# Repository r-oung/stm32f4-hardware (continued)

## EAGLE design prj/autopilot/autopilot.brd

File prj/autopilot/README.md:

# Autopilot
A drone autopilot using the STM32F4 microcontroller.

The firmware for this project can be found in the [stm32f4-firmware repository](https://github.com/r-oung/stm32f4-firmware).

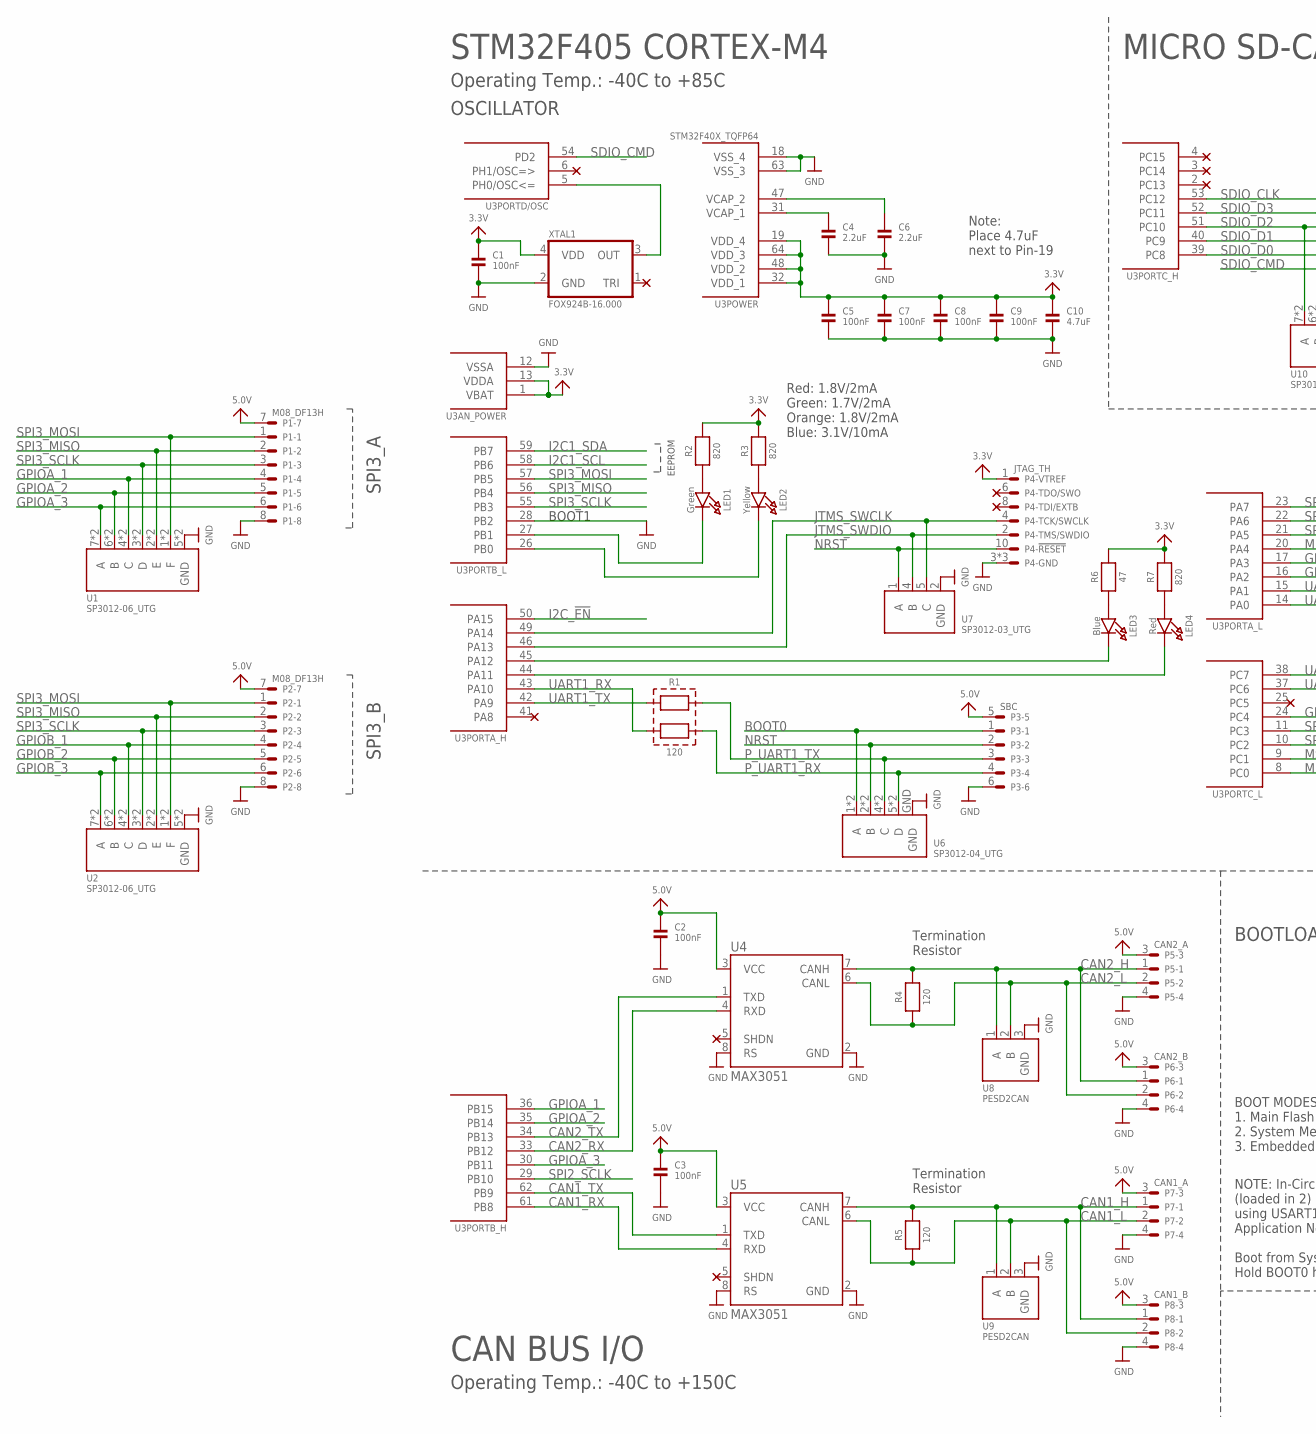
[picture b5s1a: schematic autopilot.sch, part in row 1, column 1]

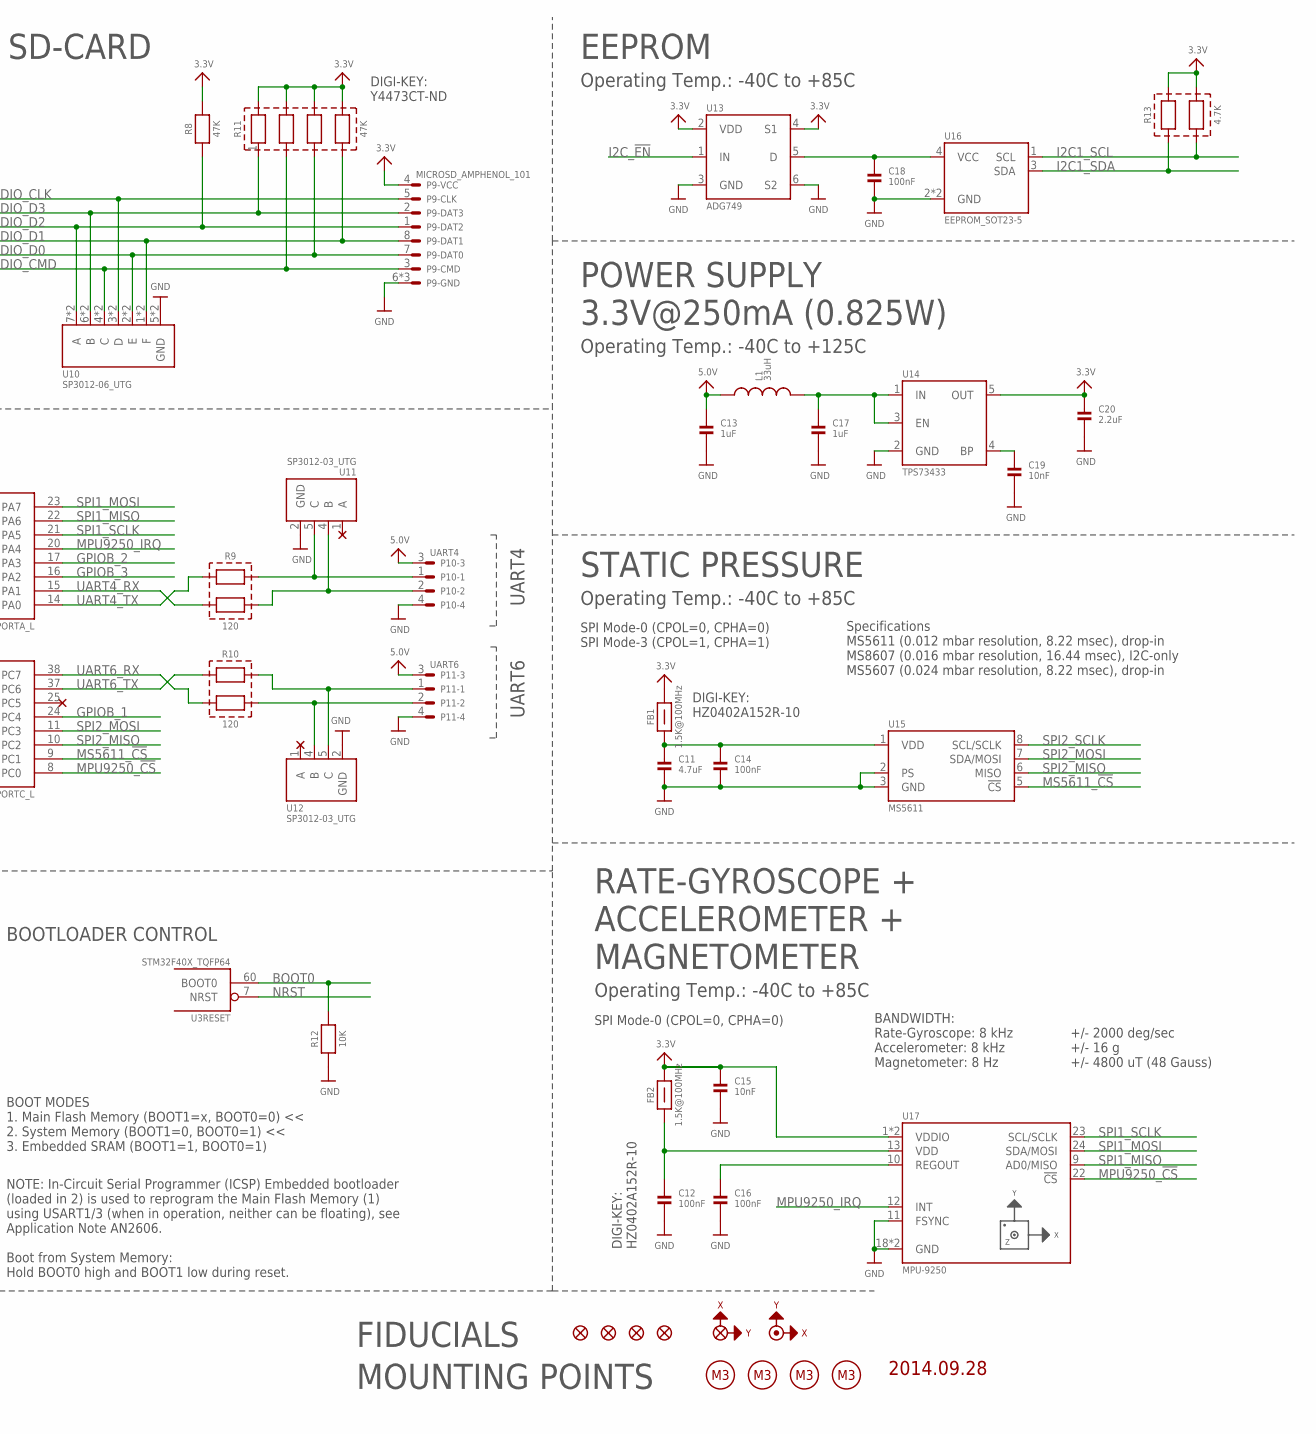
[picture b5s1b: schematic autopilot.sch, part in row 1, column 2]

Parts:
AXIS3D1: AXIS3D_DOWN
AXIS3D2: AXIS3D_UP
C1, C2, C3, C5, C7, C8, C9, C12, C14, C16, C18: 100nF; 0402
C4, C6, C20: 2.2uF; 0402
C10, C11: 4.7uF; 0402
C13, C17: 1uF; 0402
C15, C19: 10nF; 0402
FB1, FB2: 1.5K@100MHz; 0402
L1: 33uH; 1210
LED1: Green; CHIPLED_0603
LED2: Yellow; CHIPLED_0603
LED3: Blue; CHIPLED_0603
LED4: Red; CHIPLED_0603
MP1, MP2, MP3, MP4: M3; MP_M3
P1, P2: M08_DF13H; DF13A-8P-1.25H
P3: SBC; DF13A-6P-1.25H
P4: JTAG_TH; FTSH-105-01-XXX-DV
P5: CAN2_A; DF13A-4P-1.25H
P6: CAN2_B; DF13A-4P-1.25H
P7: CAN1_A; DF13A-4P-1.25H
P8: CAN1_B; DF13A-4P-1.25H
P9: MICROSD_AMPHENOL_101; AMPHENOL_101-00660-68
P10: UART4; DF13A-4P-1.25H
P11: UART6; DF13A-4P-1.25H
R1, R9, R10: 120; EXBV4V
R2, R3, R7: 820; 0402
R4, R5: 120; 0603
R6: 47; 0402
R8: 47K; 0603
R11: 47K; EXBV8V
R12: 10K; 0402
R13: 4.7K; EXBV4V
REF1, REF2, REF3, REF4: FIDUCIAL1X2.5; POINT-1MM
U1, U2, U10: SP3012-06_UTG; UDFN14
U3: STM32F40X_TQFP64; TQFP64
U4, U5: MAX3051; SOT23-8
U6: SP3012-04_UTG; UDFN10
U7, U11, U12: SP3012-03_UTG; UDFN06
U8, U9: PESD2CAN; SOT23-3
U13: ADG749; SOT-363
U14: TPS73433; SOT23-5
U15: MS5611
U16: EEPROM_SOT23-5; SOT23-5
U17: MPU-9250; MPU-3X3
XTAL1: FOX924B-16.000; OSCILLATOR-5.0X3.2A

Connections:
3.3V: C1.1, C5.1, C7.1, C8.1, C9.1, C10.1, C15.1, C20.1, FB1.2, FB2.2, P4.1, P9.4, R2.2, R3.2, R6.2, R7.2, R8.2, R11.5, R11.6, R11.7, R11.8, R13.3, R13.4, U3.1 (VBAT), U3.13 (VDDA), U3.19 (VDD_4), U3.32 (VDD_1), U3.48 (VDD_2), U3.64 (VDD_3), U13.2 (VDD), U13.4 (S1), U14.5 (OUT), U17.1 (VDDIO), U17.8 (VDDIO), XTAL1.4 (VDD)
5.0V: C2.1, C3.1, C13.1, L1.1, P1.7, P2.7, P3.5, P5.3, P6.3, P7.3, P8.3, P10.3, P11.3, U4.3 (VCC), U5.3 (VCC)
BOOT0: P3.1, R12.2, U3.60 (BOOT0), U6.1 (A), U6.10 (A)
CAN1_H: P7.1, P8.1, R5.2, U5.7 (CANH), U9.1 (A)
CAN1_L: P7.2, P8.2, R5.1, U5.6 (CANL), U9.2 (B)
CAN1_RX: U3.61 (PB8), U5.4 (RXD)
CAN1_TX: U3.62 (PB9), U5.1 (TXD)
CAN2_H: P5.1, P6.1, R4.2, U4.7 (CANH), U8.1 (A)
CAN2_L: P5.2, P6.2, R4.1, U4.6 (CANL), U8.2 (B)
CAN2_RX: U3.33 (PB12), U4.4 (RXD)
CAN2_TX: U3.34 (PB13), U4.1 (TXD)
GND: C1.2, C2.2, C3.2, C4.2, C5.2, C6.2, C7.2, C8.2, C9.2, C10.2, C11.2, C12.2, C13.2, C14.2, C15.2, C16.2, C17.2, C18.2, C19.2, C20.2, P1.8, P2.8, P3.6, P4.3, P4.5, P4.9, P5.4, P6.4, P7.4, P8.4, P9.6, P9.GND1, P9.GND3, P10.4, P11.4, R12.1, U1.5 (GND), U1.10 (GND), U2.5 (GND), U2.10 (GND), U3.12 (VSSA), U3.18 (VSS_4), U3.28 (PB2), U3.63 (VSS_3), U4.2 (GND), U4.8 (RS), U5.2 (GND), U5.8 (RS), U6.GND, U7.2 (GND), U8.3 (GND), U9.3 (GND), U10.5 (GND), U10.10 (GND), U11.2 (GND), U12.2 (GND), U13.3 (GND), U13.6 (S2), U14.2 (GND), U15.2 (PS), U15.3 (GND), U16.2 (GND), U16.5 (GND), U17.11 (FSYNC), U17.18 (GND), U17.20 (GND), XTAL1.2 (GND)
GPIOA_1: P1.4, U1.4 (C), U1.11 (C), U3.36 (PB15)
GPIOA_2: P1.5, U1.6 (B), U1.9 (B), U3.35 (PB14)
GPIOA_3: P1.6, U1.7 (A), U1.8 (A), U3.30 (PB11)
GPIOB_1: P2.4, U2.4 (C), U2.11 (C), U3.24 (PC4)
GPIOB_2: P2.5, U2.6 (B), U2.9 (B), U3.17 (PA3)
GPIOB_3: P2.6, U2.7 (A), U2.8 (A), U3.16 (PA2)
I2C1_SCL: R13.2, U3.58 (PB6), U16.1 (SCL)
I2C1_SDA: R13.1, U3.59 (PB7), U16.3 (SDA)
I2C_!EN: U3.50 (PA15), U13.1 (IN)
JTMS_SWCLK: P4.4, U3.49 (PA14), U7.5 (C)
JTMS_SWDIO: P4.2, U3.46 (PA13), U7.4 (B)
MPU9250_!CS: U3.8 (PC0), U17.22 (!CS)
MPU9250_IRQ: U3.20 (PA4), U17.12 (INT)
MS5611_!CS: U3.9 (PC1), U15.5 (!CS)
unnamed: LED4.A, R7.1
unnamed: LED1.A, R2.1
unnamed: LED2.A, R3.1
unnamed: C16.1, U17.10 (REGOUT)
unnamed: LED3.A, R6.1
unnamed: C12.1, FB2.1, U17.13 (VDD)
unnamed: LED3.C, U3.45 (PA12)
unnamed: U3.5 (PH0/OSC<=), XTAL1.3 (OUT)
unnamed: C18.1, U13.5 (D), U16.4 (VCC)
unnamed: C19.1, U14.4 (BP)
unnamed: LED4.C, U3.44 (PA11)
unnamed: LED1.C, U3.27 (PB1)
unnamed: LED2.C, U3.26 (PB0)
unnamed: C17.1, L1.2, U14.1 (IN), U14.3 (EN)
NRST: P3.2, P4.10, U3.7 (NRST), U6.2 (B), U6.9 (B), U7.1 (A)
P_UART1_RX: P3.4, R1.3, U6.5 (D), U6.6 (D)
P_UART1_TX: P3.3, R1.4, U6.4 (C), U6.7 (C)
P_UART4_RX: P10.2, R9.3, U11.4 (B)
P_UART4_TX: P10.1, R9.4, U11.5 (C)
P_UART6_RX: P11.2, R10.3, U12.4 (B)
P_UART6_TX: P11.1, R10.4, U12.5 (C)
SDIO_CLK: P9.5, U3.53 (PC12), U10.3 (D), U10.12 (D)
SDIO_CMD: P9.3, R11.2, U3.54 (PD2), U10.4 (C), U10.11 (C)
SDIO_D0: P9.7, R11.3, U3.39 (PC8), U10.2 (E), U10.13 (E)
SDIO_D1: P9.8, R11.4, U3.40 (PC9), U10.1 (F), U10.14 (F)
SDIO_D2: P9.1, R8.1, U3.51 (PC10), U10.7 (A), U10.8 (A)
SDIO_D3: P9.2, R11.1, U3.52 (PC11), U10.6 (B), U10.9 (B)
SPI1_MISO: U3.22 (PA6), U17.9 (AD0/MISO)
SPI1_MOSI: U3.23 (PA7), U17.24 (SDA/MOSI)
SPI1_SCLK: U3.21 (PA5), U17.23 (SCL/SCLK)
SPI2_MISO: U3.10 (PC2), U15.6 (MISO)
SPI2_MOSI: U3.11 (PC3), U15.7 (SDA/MOSI)
SPI2_SCLK: U3.29 (PB10), U15.8 (SCL/SCLK)
SPI3_MISO: P1.2, P2.2, U1.2 (E), U1.13 (E), U2.2 (E), U2.13 (E), U3.56 (PB4)
SPI3_MOSI: P1.1, P2.1, U1.1 (F), U1.14 (F), U2.1 (F), U2.14 (F), U3.57 (PB5)
SPI3_SCLK: P1.3, P2.3, U1.3 (D), U1.12 (D), U2.3 (D), U2.12 (D), U3.55 (PB3)
UART1_RX: R1.2, U3.43 (PA10)
UART1_TX: R1.1, U3.42 (PA9)
UART4_RX: R9.2, U3.15 (PA1)
UART4_TX: R9.1, U3.14 (PA0)
UART6_RX: R10.2, U3.38 (PC7)
UART6_TX: R10.1, U3.37 (PC6)
VCAP_1: C4.1, U3.31 (VCAP_1)
VCAP_2: C6.1, U3.47 (VCAP_2)
VDD_PRES: C11.1, C14.1, FB1.1, U15.1 (VDD)

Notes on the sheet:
RATE-GYROSCOPE + ACCELEROMETER + MAGNETOMETER
STATIC PRESSURE
STM32F405 CORTEX-M4
Operating Temp.: -40C to +85C
BOOTLOADER CONTROL
OSCILLATOR
BOOT1
EEPROM
Red: 1.8V/2mA Green: 1.7V/2mA Orange: 1.8V/2mA Blue: 3.1V/10mA
DIGI-KEY: HZ0402A152R-10
Note: Place 4.7uF next to Pin-19
BOOT MODES 1. Main Flash Memory (BOOT1=x, BOOT0=0) << 2. System Memory (BOOT1=0, BOOT0=1) << 3. Embedded SRAM (BOOT1=1, BOOT0=1)
NOTE: In-Circuit Serial Programmer (ICSP) Embedded bootloader (loaded in 2) is used to reprogram the Main Flash Memory (1) using USART1/3 (when in operation, neither can be floating), see Application Note AN2606. Boot from System Memory: Hold BOOT0 high and BOOT1 low during reset.
+/- 2000 deg/sec +/- 16 g +/- 4800 uT (48 Gauss)
BANDWIDTH: Rate-Gyroscope: 8 kHz Accelerometer: 8 kHz Magnetometer: 8 Hz
Specifications MS5611 (0.012 mbar resolution, 8.22 msec), drop-in MS8607 (0.016 mbar resolution, 16.44 msec), I2C-only MS5607 (0.024 mbar resolution, 8.22 msec), drop-in
SPI Mode-0 (CPOL=0, CPHA=0) SPI Mode-3 (CPOL=1, CPHA=1)
SPI Mode-0 (CPOL=0, CPHA=0)
POWER SUPPLY 3.3V@250mA (0.825W)
Operating Temp.: -40C to +125C
Operating Temp.: -40C to +150C
CAN BUS I/O
Termination Resistor
MOUNTING POINTS
FIDUCIALS
SPI3_A
UART4
UART6
DIGI-KEY: Y4473CT-ND
MICRO SD-CARD
SPI3_B
2014.09.28

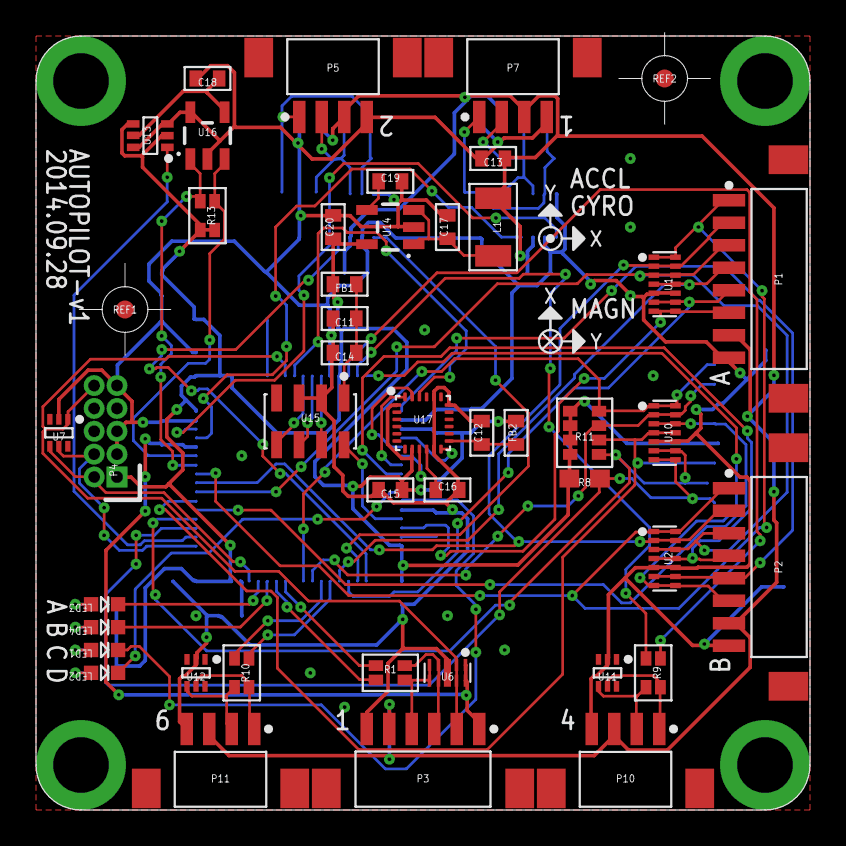
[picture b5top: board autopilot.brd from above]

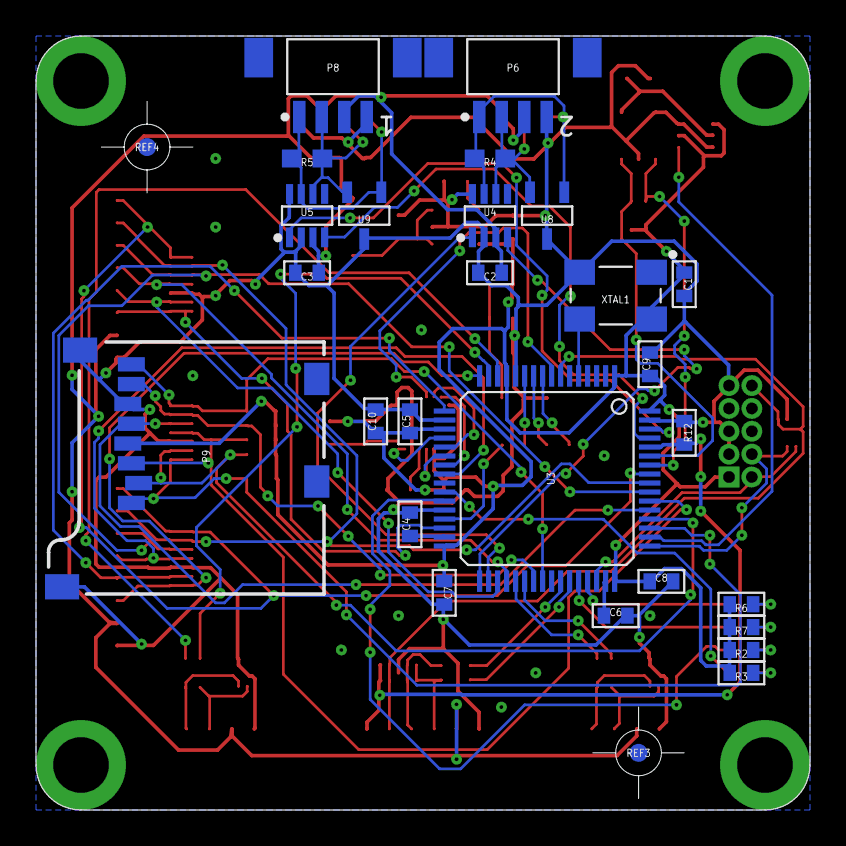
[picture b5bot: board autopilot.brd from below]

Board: 2 copper layers, 43.0 x 43.0 mm, 79 parts (28 on the bottom side), 71 nets.

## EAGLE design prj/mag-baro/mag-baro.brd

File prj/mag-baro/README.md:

# Magnetometer-Barometer
A PCB containing both a 3-axis magnetometer and barometer with CAN-bus communication.

The firmware for this project can be found in the [stm32f4-firmware repository](https://github.com/r-oung/stm32f4-firmware).

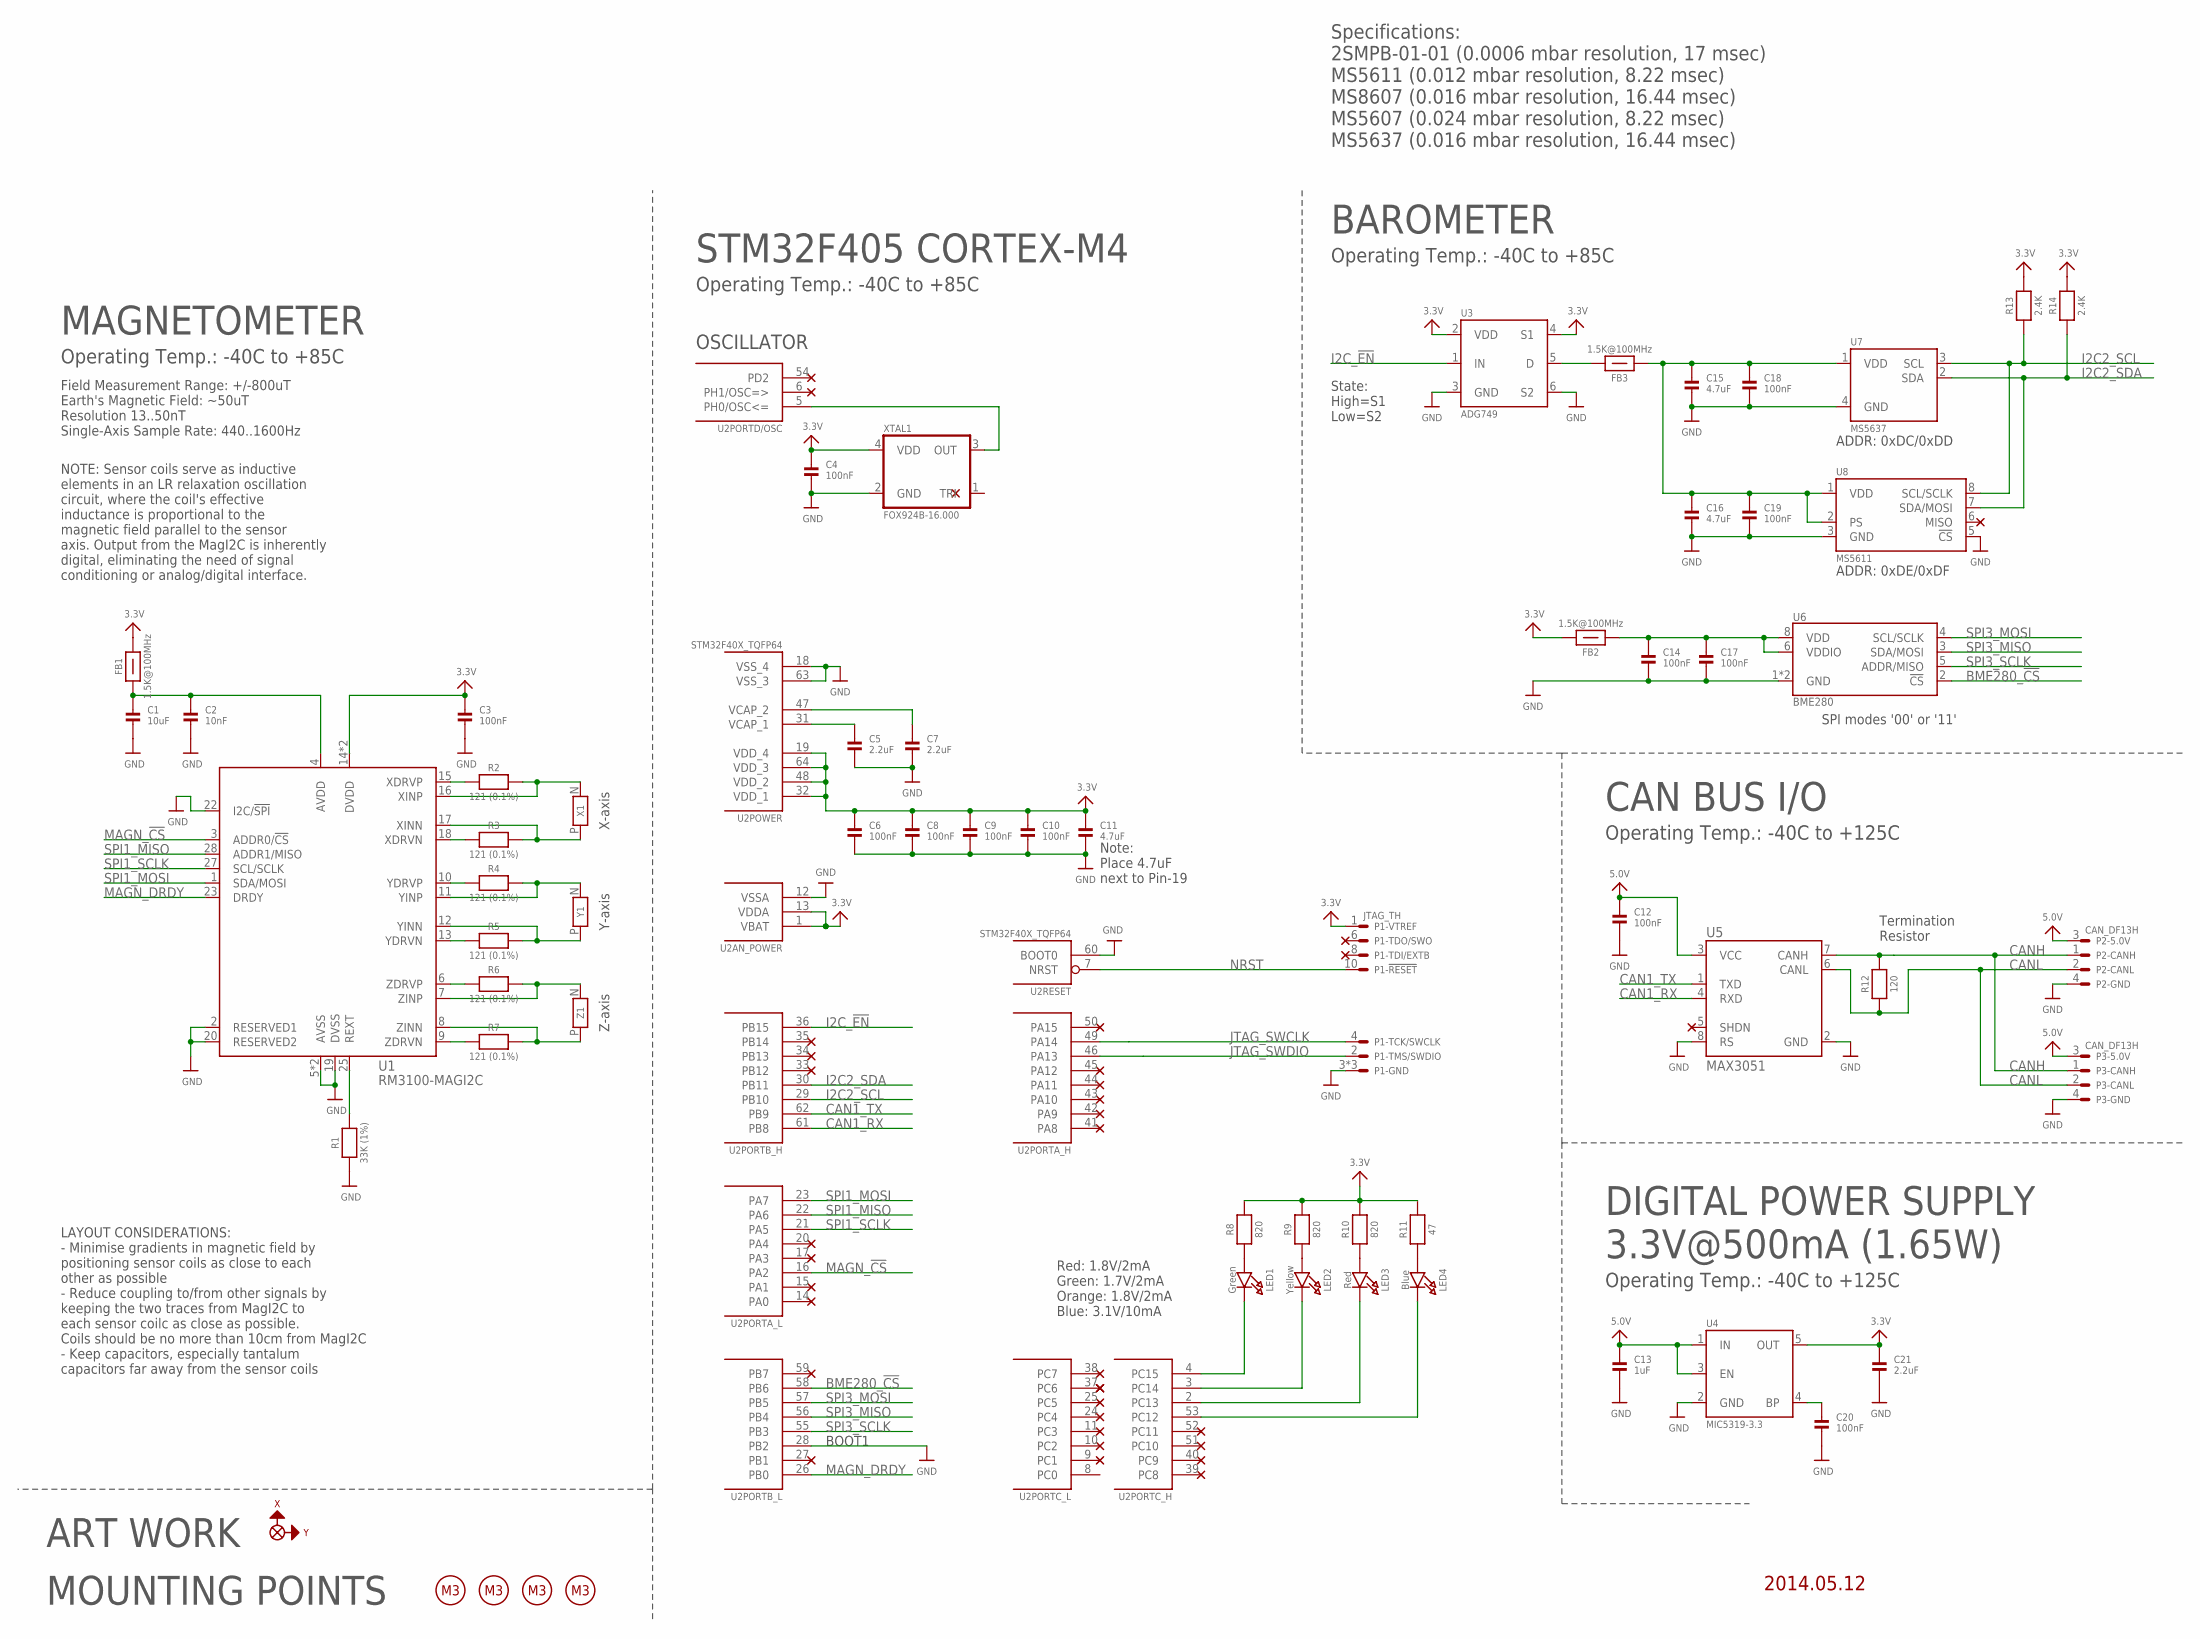
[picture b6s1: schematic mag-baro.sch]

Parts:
AXIS3D2: AXIS3D_DOWN
C1: 10uF; 0402
C2: 10nF; 0402
C3, C4, C6, C8, C9, C10, C12, C14, C17, C18, C19, C20: 100nF; 0402
C5, C7, C21: 2.2uF; 0402
C11, C15, C16: 4.7uF; 0402
C13: 1uF; 0402
FB1, FB2, FB3: 1.5K@100MHz; 0402
LED1: Green; CHIPLED_0603
LED2: Yellow; CHIPLED_0603
LED3: Red; CHIPLED_0603
LED4: Blue; CHIPLED_0603
MP1, MP2, MP3, MP4: M3_5; MP_M3-5
P1: JTAG_TH; FTSH-105-01-XXX-DV
P2, P3: CAN_DF13H; DF13A-4P-1.25H
R1: 33K (1%); 0402
R2, R3, R4, R5, R6, R7: 121 (0.1%); 0402
R8, R9, R10: 820; 0402
R11: 47; 0402
R12: 120; 0603
R13, R14: 2.4K; 0402
U1: RM3100-MAGI2C
U2: STM32F40X_TQFP64; TQFP64
U3: ADG749; SOT363
U4: MIC5319-3.3; SOT23-5
U5: MAX3051; SOT23-8
U6: BME280; BME280_LGA_MANUAL
U7: MS5637
U8: MS5611
X1: RM3XXX-SEN-X; RM3XXX-SEN-XY
XTAL1: FOX924B-16.000; OSCILLATOR-5.0X3.2A
Y1: RM3XXX-SEN-Y; RM3XXX-SEN-XY
Z1: RM3XXX-SEN-Z; RM3XXX-SEN_Z

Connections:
3.3V: C3.1, C4.1, C6.1, C8.1, C9.1, C10.1, C11.1, C21.1, FB1.2, FB2.2, P1.1, R8.2, R9.2, R10.2, R11.2, R13.2, R14.2, U1.14 (DVDD), U1.26 (DVDD), U2.1 (VBAT), U2.13 (VDDA), U2.19 (VDD_4), U2.32 (VDD_1), U2.48 (VDD_2), U2.64 (VDD_3), U3.2 (VDD), U3.4 (S1), U4.5 (OUT), XTAL1.4 (VDD)
5.0V: C12.1, C13.1, P2.3, P3.3, U4.1 (IN), U4.3 (EN), U5.3 (VCC)
A3.3V: C1.1, C2.1, FB1.1, U1.4 (AVDD)
BME280_!CS: U2.58 (PB6), U6.2 (!CS)
CAN1_RX: U2.61 (PB8), U5.4 (RXD)
CAN1_TX: U2.62 (PB9), U5.1 (TXD)
CANH: P2.1, P3.1, R12.2, U5.7 (CANH)
CANL: P2.2, P3.2, R12.1, U5.6 (CANL)
GND: C1.2, C2.2, C3.2, C4.2, C5.2, C6.2, C7.2, C8.2, C9.2, C10.2, C11.2, C12.2, C13.2, C14.2, C15.2, C16.2, C17.2, C18.2, C19.2, C20.2, C21.2, P1.3, P1.5, P1.9, P2.4, P3.4, R1.1, U1.2 (RESERVED1), U1.5 (AVSS), U1.19 (DVSS), U1.20 (RESERVED2), U1.22 (I2C/!SPI), U1.PAD (AVSS), U2.12 (VSSA), U2.18 (VSS_4), U2.28 (PB2), U2.60 (BOOT0), U2.63 (VSS_3), U3.3 (GND), U3.6 (S2), U4.2 (GND), U5.2 (GND), U5.8 (RS), U6.1 (GND), U6.7 (GND), U7.4 (GND), U8.3 (GND), U8.5 (!CS), XTAL1.2 (GND)
I2C2_SCL: R13.1, U2.29 (PB10), U7.3 (SCL), U8.8 (SCL/SCLK)
I2C2_SDA: R14.1, U2.30 (PB11), U7.2 (SDA), U8.7 (SDA/MOSI)
I2C_!EN: U2.36 (PB15), U3.1 (IN)
JTAG_SWCLK: P1.4, U2.49 (PA14)
JTAG_SWDIO: P1.2, U2.46 (PA13)
MAGN_!CS: U1.3 (ADDR0/!CS), U2.16 (PA2)
MAGN_DRDY: U1.23 (DRDY), U2.26 (PB0)
unnamed: R1.2, U1.25 (REXT)
unnamed: C15.1, C16.1, C18.1, C19.1, FB3.1, U7.1 (VDD), U8.1 (VDD), U8.2 (PS)
unnamed: C14.1, C17.1, FB2.1, U6.6 (VDDIO), U6.8 (VDD)
unnamed: LED1.C, U2.4 (PC15)
unnamed: C20.1, U4.4 (BP)
unnamed: R2.1, U1.15 (XDRVP)
unnamed: R3.1, U1.18 (XDRVN)
unnamed: R2.2, U1.16 (XINP), X1.N
unnamed: FB3.2, U3.5 (D)
unnamed: U2.5 (PH0/OSC<=), XTAL1.3 (OUT)
unnamed: R3.2, U1.17 (XINN), X1.P
unnamed: LED1.A, R8.1
unnamed: LED2.A, R9.1
unnamed: LED4.A, R11.1
unnamed: LED2.C, U2.3 (PC14)
unnamed: LED3.C, U2.2 (PC13)
unnamed: LED4.C, U2.53 (PC12)
unnamed: LED3.A, R10.1
unnamed: R6.2, U1.7 (ZINP), Z1.N
unnamed: R4.1, U1.10 (YDRVP)
unnamed: R5.1, U1.13 (YDRVN)
unnamed: R6.1, U1.6 (ZDRVP)
unnamed: R7.1, U1.9 (ZDRVN)
unnamed: R4.2, U1.11 (YINP), Y1.N
unnamed: R5.2, U1.12 (YINN), Y1.P
unnamed: R7.2, U1.8 (ZINN), Z1.P
NRST: P1.10, U2.7 (NRST)
SPI1_MISO: U1.28 (ADDR1/MISO), U2.22 (PA6)
SPI1_MOSI: U1.1 (SDA/MOSI), U2.23 (PA7)
SPI1_SCLK: U1.27 (SCL/SCLK), U2.21 (PA5)
SPI3_MISO: U2.56 (PB4), U6.5 (ADDR/MISO)
SPI3_MOSI: U2.57 (PB5), U6.3 (SDA/MOSI)
SPI3_SCLK: U2.55 (PB3), U6.4 (SCL/SCLK)
VCAP_1: C5.1, U2.31 (VCAP_1)
VCAP_2: C7.1, U2.47 (VCAP_2)

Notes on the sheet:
MAGNETOMETER
Operating Temp.: -40C to +85C
Field Measurement Range: +/-800uT Earth's Magnetic Field: ~50uT Resolution 13..50nT Single-Axis Sample Rate: 440..1600Hz
X-axis
Y-axis
Z-axis
STM32F405 CORTEX-M4
OSCILLATOR
BOOT1
Red: 1.8V/2mA Green: 1.7V/2mA Orange: 1.8V/2mA Blue: 3.1V/10mA
Note: Place 4.7uF next to Pin-19
MOUNTING POINTS
ART WORK
DIGITAL POWER SUPPLY 3.3V@500mA (1.65W)
Operating Temp.: -40C to +125C
CAN BUS I/O
Termination Resistor
NOTE: Sensor coils serve as inductive elements in an LR relaxation oscillation circuit, where the coil's effective inductance is proportional to the magnetic field parallel to the sensor axis. Output from the MagI2C is inherently digital, eliminating the need of signal conditioning or analog/digita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
LAYOUT CONSIDERATIONS: - Minimise gradients in magnetic field by positioning sensor coils as close to each other as possible - Reduce coupling to/from other signals by keeping the two traces from MagI2C to each sensor coilc as close as possible. Coils should be no more than 10cm from MagI2C - Keep 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
ADDR: 0xDC/0xDD
ADDR: 0xDE/0xDF
BAROMETER
Specifications: 2SMPB-01-01 (0.0006 mbar resolution, 17 msec) MS5611 (0.012 mbar resolution, 8.22 msec) MS8607 (0.016 mbar resolution, 16.44 msec) MS5607 (0.024 mbar resolution, 8.22 msec) MS5637 (0.016 mbar resolution, 16.44 msec)
State: High=S1 Low=S2
SPI modes '00' or '11'
2014.05.12

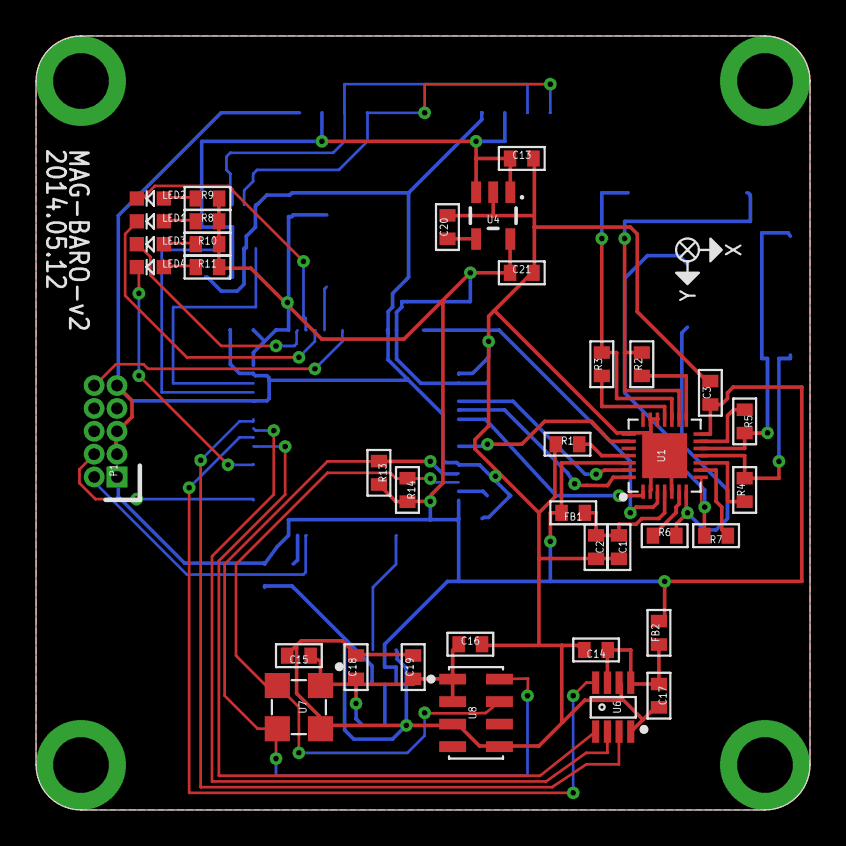
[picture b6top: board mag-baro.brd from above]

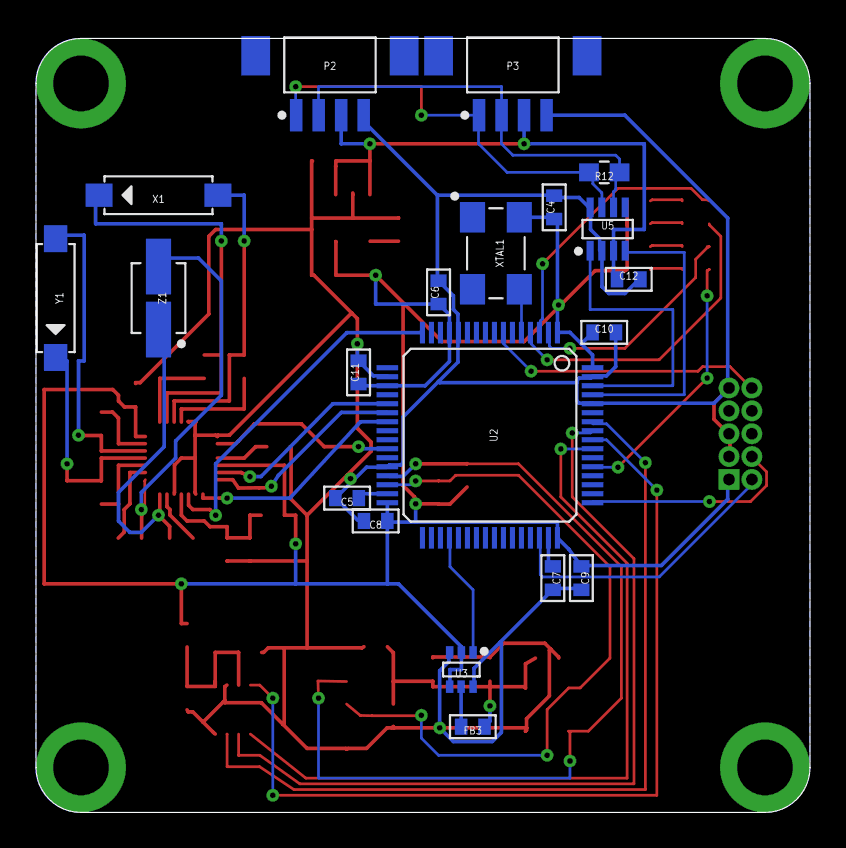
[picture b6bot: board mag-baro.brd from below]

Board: 2 copper layers, 43.0 x 43.0 mm, 62 parts (20 on the bottom side), 51 nets.

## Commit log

2022-02-04 Updates README
2022-02-17 Adds rpi-lirc
2022-02-17 Adds README file to each project
2023-04-03 Adds eagle-assets submodule
